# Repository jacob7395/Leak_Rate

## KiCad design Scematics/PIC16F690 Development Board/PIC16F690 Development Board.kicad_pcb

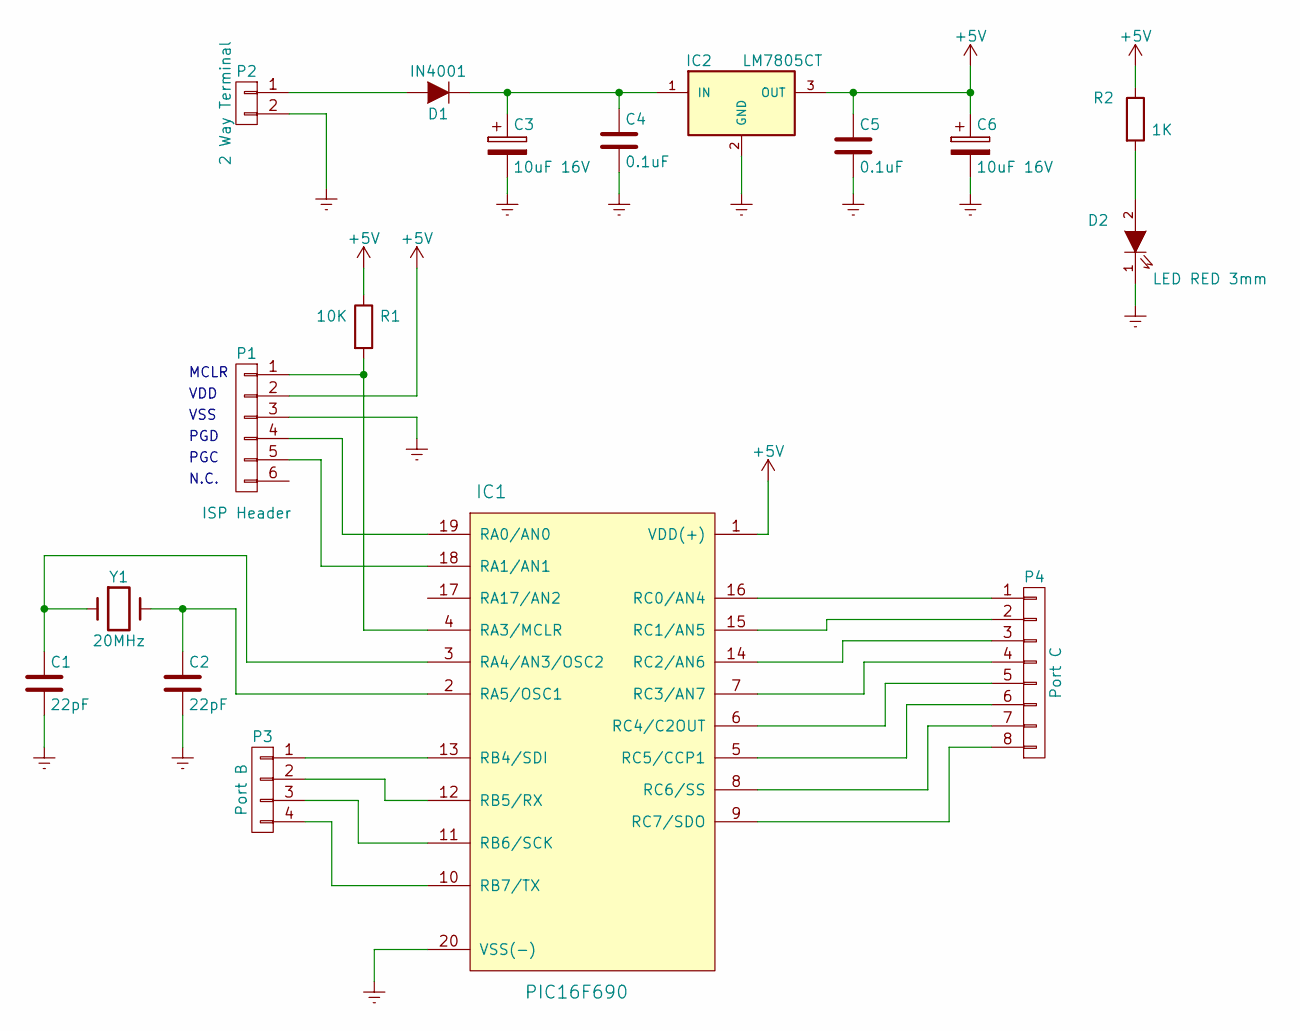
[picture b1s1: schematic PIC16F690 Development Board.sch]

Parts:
C1, C2: 22pF; Capacitor_01_Single_Sided
C3, C6: 10uF 16V; Capacitor_Electrolytic_Small_Single_Sided
C4, C5: 0.1uF; Capacitor_02_Single_Sided
D1: IN4001; Diode_Single_Sided
D2: LED RED 3mm; LED_3mm_Single_Sided
IC1: PIC16F690; DIL_20_Single_Sided
IC2: LM7805CT; 7805_TO220_Single_Sided
P1: ISP Header; Header_6W_Single_Sided
P2: 2 Way Terminal; Terminal_2W_Single_Sided
P3: Port B; Header_4W_Single_Sided
P4: Port C; Header_8W_Single_Sided
R1: 10K; Resistor_Single_Sided
R2: 1K; Resistor_Single_Sided
Y1: 20MHz; Crystal_HC49_Single_Sided

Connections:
+5V: C5.1, C6.1, IC1.1 (VDD(+)), IC2.3 (OUT), P1.2, R1.1, R2.1
Earth: C1.2, C2.2, C3.2, C4.2, C5.2, C6.2, D2.1 (K), IC1.20 (VSS(-)), IC2.2 (GND), P1.3, P2.2
unnamed: C1.1, IC1.3 (RA4/AN3/OSC2), Y1.1
unnamed: C2.1, IC1.2 (RA5/OSC1), Y1.2
unnamed: C3.1, C4.1, D1.1 (K), IC2.1 (IN)
unnamed: D1.2 (A), P2.1
unnamed: D2.2 (A), R2.2
unnamed: IC1.4 (RA3/MCLR), P1.1, R1.2
unnamed: IC1.5 (RC5/CCP1), P4.6
unnamed: IC1.6 (RC4/C2OUT), P4.5
unnamed: IC1.7 (RC3/AN7), P4.4
unnamed: IC1.8 (RC6/SS), P4.7
unnamed: IC1.9 (RC7/SDO), P4.8
unnamed: IC1.10 (RB7/TX), P3.4
unnamed: IC1.11 (RB6/SCK), P3.3
unnamed: IC1.12 (RB5/RX), P3.2
unnamed: IC1.13 (RB4/SDI), P3.1
unnamed: IC1.14 (RC2/AN6), P4.3
unnamed: IC1.15 (RC1/AN5), P4.2
unnamed: IC1.16 (RC0/AN4), P4.1
unnamed: IC1.18 (RA1/AN1), P1.5
unnamed: IC1.19 (RA0/AN0), P1.4

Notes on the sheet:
MCLR
VDD
VSS
PGD
PGC
N.C.

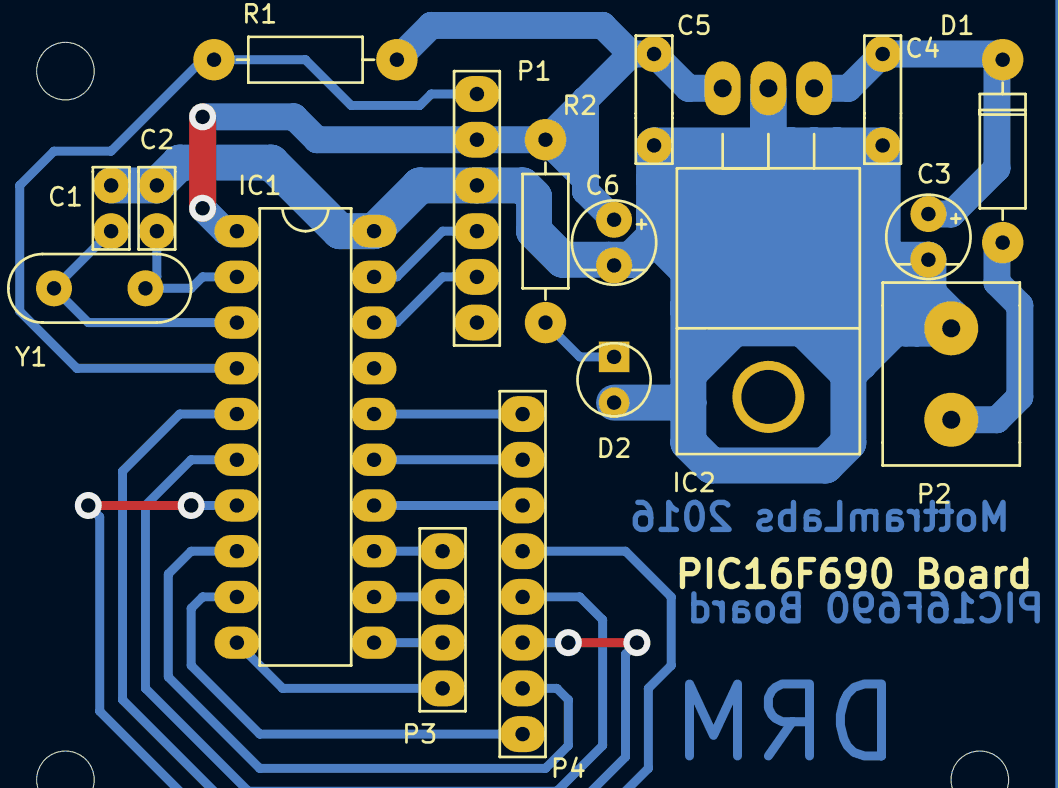
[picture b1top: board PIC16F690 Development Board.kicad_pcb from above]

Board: 2 copper layers, 17 parts (0 on the bottom side), 22 nets.

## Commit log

2016-08-11 Initial Uplode
    Schematics for Dave’s photo board.
    Test code in file Leak.rate(using others libers)
    Data Sheet for the pic16f1769
    Data Sheet for the PCF8574 i2c/IO chip
    Run time code in folder Leak functionality for-
    basic pin initialisation
2016-08-12 Done: working time test code in main with interupts
    To-do:
    Setup interup c file
    Setup timer c file
    implement working LCD communication protocols using timer2
2016-08-12 CLEANUP Done: made a system init to organize all system setup
    To-do:
    Setup interup c file
    Setup timer c file
    implement working LCD communication protocols using timer2
2016-08-12 ADDITION Done: Made timer c file: -Implomented code for wait between 0-255 µ seconds
    To-do:
    Setup interup c file
    implement working LCD communication protocols using timer2
2016-08-12 UPDATE Full project commit
    Done:
    Made timer c file:
    -Implomented code for wait between 0-255 µ seconds
    To-do:
    Setup interup c file
    implement working LCD communication protocols using timer2
2016-08-12 DATA-SHEET
    added LCD data-sheet
2016-08-15 UPDATE Full project commit
    Done:
    Made timer c file:
    -Implemented time1 code allowing waits from 0-65535 micro seconds needed for LCD control
    To-do:
    Setup interup c file
    implement working LCD communication protocols using timer2
2016-08-16 UPDATE
    Done:
    LCD init working, currently testing data write command
    To-do:
    Setup interup c file
    implement working LCD communication protocols using timer2
2016-08-17 UPDATE
    Done:
    Setup interup c file
    begun construction of LCD state mechine and implomented Interrup
    To-do:
    Build LCD state machine
2016-08-19 UPDATE
    Done:
    Built LCD state machine with sucsesful page set and page scroll test
    To-do:
    Implomnet button/dile code
    Imploment LCD control with button/dile
